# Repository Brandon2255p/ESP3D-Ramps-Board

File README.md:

# ESP3D-Ramps-Board
This is a simple adapter board for the ESP8266 to plug into the Ramps 1.4. When coupled with [ESP3D](https://github.com/luc-github/ESP3D) or other firmware this board will provide a wifi to serial connection for 3D printers

This board is designed for the ESP8266-12E, ESP8266-12F, ESP8266-12S models.

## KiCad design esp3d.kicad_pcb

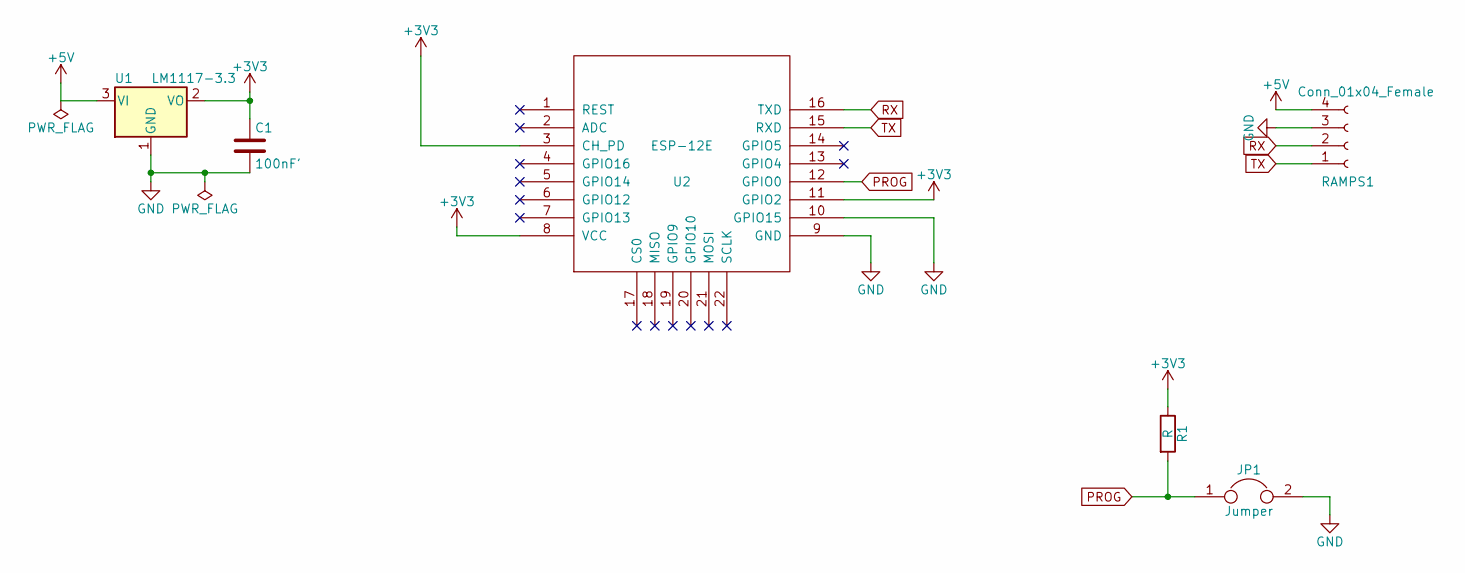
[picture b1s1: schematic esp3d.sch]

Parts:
C1: 100nF'; C_0805_HandSoldering
JP1: Jumper; Resistor_SMDuniversal_0805to2512_HandSoldering
R1: R; R_0805_HandSoldering
RAMPS1: Conn_01x04_Female; Socket_Strip_Straight_1x04_Pitch2.54mm
U1: LM1117-3.3; SOT-223-3_TabPin2
U2: ESP-12E; ESP-12S_SMD

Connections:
+3V3: C1.1, R1.1, U1.2 (VO), U2.3 (CH_PD), U2.8 (VCC), U2.11 (GPIO2)
+5V: RAMPS1.4, U1.3 (VI)
GND: C1.2, JP1.2, RAMPS1.3, U1.1 (GND), U2.9 (GND), U2.10 (GPIO15)
PROG: JP1.1, R1.2, U2.12 (GPIO0)
RX: RAMPS1.2, U2.16 (TXD)
TX: RAMPS1.1, U2.15 (RXD)

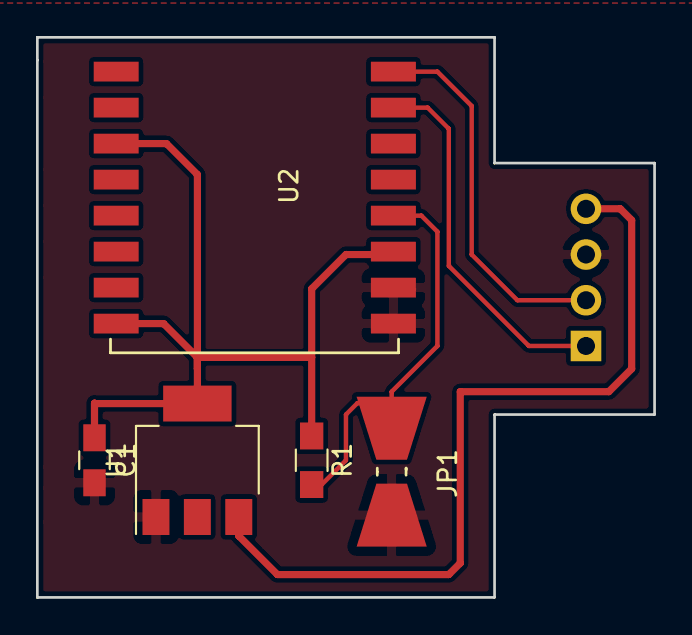
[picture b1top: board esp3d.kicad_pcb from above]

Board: 2 copper layers, 34.3 x 31.1 mm, 6 parts (1 on the bottom side), 6 nets.

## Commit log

2017-12-03 Added initial design
2017-12-03 Reversed the ramps connector. Removed resistors that may have prevented programming
